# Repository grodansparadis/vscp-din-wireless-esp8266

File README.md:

# vscp-din-wireless-esp8266
ESP8266 based VSCP controller in one module DIN package. The usage for the modul is to interface a P1 electricity meter and report meter readings over VSCP.

Can be powered from the meter or externally.

**Note!** This is still a prototype.

## PCB's

---

Part of the [VSCP Project](https://www.vscp.org).

Copyright 2021-2022 © Åke Hedman, (Grodans Paradis AB)[https://www.grodansparadis.com]

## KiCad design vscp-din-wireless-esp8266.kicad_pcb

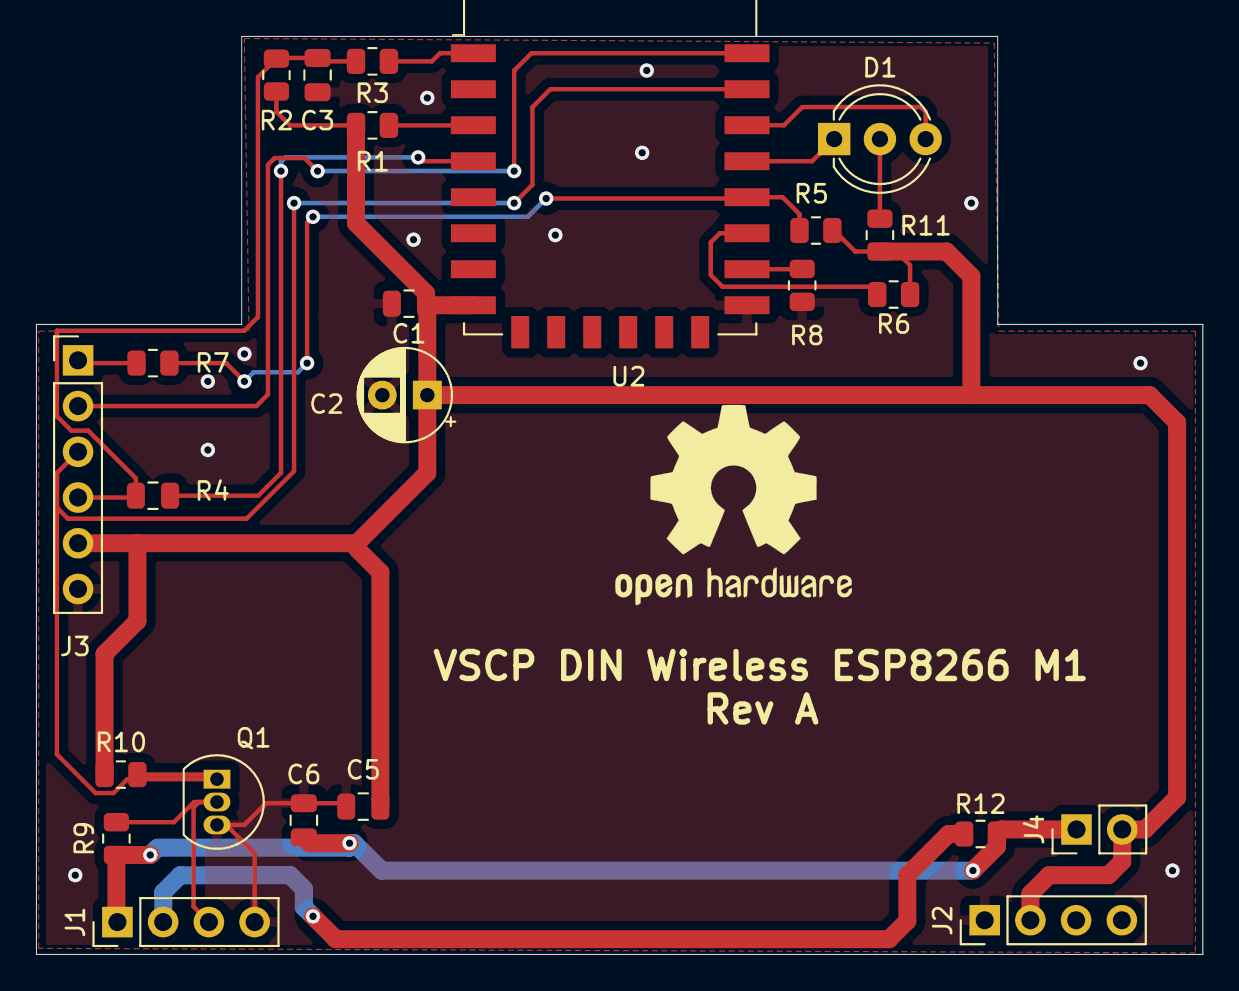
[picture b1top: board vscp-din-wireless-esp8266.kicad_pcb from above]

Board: 2 copper layers, 64.8 x 51.0 mm, 24 parts (0 on the bottom side), 18 nets.

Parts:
C1, C3, C5, C6: 100nF; C_0805_2012Metric
C2: 1000uF; CP_Radial_D5.0mm_P2.50mm
D1: LED_Dual_CAC; LED_D5.0mm-3
J1: Conn_01x04_Left; PinHeader_1x04_P2.54mm_Vertical
J2: Conn_01x04_Right; PinHeader_1x04_P2.54mm_Vertical
J3: Conn_01x06; PinHeader_1x06_P2.54mm_Vertical
J4: Conn_01x02; PinHeader_1x02_P2.54mm_Vertical
Q1: BC547; TO-92_Inline
R1, R2, R5, R6, R8, R10: 10K; R_0805_2012Metric
R3, R7: 470; R_0805_2012Metric
R4: 470; C_0805_2012Metric
R9: 4k7; R_0805_2012Metric
R11: 1K; R_0805_2012Metric
R12: 0R; R_0805_2012Metric
U2: ESP-12E

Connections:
/FLASH: J3.1, R7.2
/RESET: C3.1, J3.4, R2.2, R3.2, R4.1
/RXD: J3.3, Q1.1, R10.1, U2.21
/TXD: J3.2, U2.22
/leda: D1.1, U2.19
/ledb: D1.3, U2.20
GND: C1.2, C2.2, C3.2, C5.2, C6.2, J1.4, J2.1, J3.6, Q1.3, R8.1, U2.15
unnamed: D1.2, R11.2
unnamed: J1.2, R12.1
unnamed: J1.3, Q1.2, R9.1
unnamed: R1.2, U2.3
unnamed: R3.1, U2.1
unnamed: R4.2, U2.4
unnamed: R5.2, R7.1, U2.18
unnamed: R6.2, U2.17
unnamed: R8.2, U2.16
VCC: C1.1, C2.1, C5.1, J2.2, J3.5, J4.2, R1.1, R2.1, R5.1, R6.1, R10.2, R11.1, U2.8
VDD: C6.1, J1.1, J4.1, R9.2, R12.2

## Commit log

2021-05-24 Initial import
2021-05-24 Fixed board pictures
2021-05-25 Fixed board to board connector
2021-05-25 Adding gerbers
2021-05-25 Added info
2022-02-03 Updated copyright
